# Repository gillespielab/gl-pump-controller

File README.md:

# gl-pump-controller
This board is a SpikeGadgets ECU accessory, which acts as an RJ-45 breakout board for 8 or the DIO ports, and as a pump controller for the other 8 DIO ports in the bank. KiCAD is required to open/edit this project, and can be downloaded at https://www.kicad.org/download/

# Download Instructions
1. Clone the repo `git clone --recursive https://github.com/gillespielab/gl-pump-controller`
2. Open the KiCAD Symbol Editor. Then click: "File" -> "Add Library"
3. Select Global
4. In the prompt, select/open: gl-pump-controller/gl-electronics/symbols/Uploaded.kicad_sym

# BOM
Description | Component Number | Quantity | Part Number/Link
------------- | ------------- | ------------- | -------------
8-bit Buffer | U9-U10 | 2 | [SN74ABT541BPW](https://www.digikey.com/en/products/detail/texas-instruments/SN74ABT541BPW/1575499)
2x10 90deg Header Pins | J11 | 2 | [2057-PH2RA-20-UA-ND](https://www.digikey.com/en/products/detail/adam-tech/PH2RA-20-UA/9830622?s=N4IgTCBcDa4AwFYDsBaACgCTAJQIIrDhQFV8A5AERAF0BfIA)
8x1 RJ-45 Array | J9 | 1 | [432238182](https://www.digikey.com/en/products/detail/molex/0432238182/481095)
SSD Relays | U1-U8 | 8 | [AQY211EHAX](https://www.digikey.com/en/products/detail/panasonic-electric-works/AQY211EHAX/2804732)
1.02kO Resistor | R1-R8 | 8 | [RC1206FR-071K02L](https://www.digikey.com/en/products/detail/yageo/RC1206FR-071K02L/728390)
1uF Ceramic Capacitor | C1-C8 | 8 | [AGC1206X7R101-104KNE-CT](https://www.digikey.com/en/products/detail/venkel/AGC1206X7R101-104KNE-CT/21344624)
10kO Resistor | R9 | 1 | [ERJ-8ENF1002V](https://www.digikey.com/en/products/detail/panasonic-electronic-components/ERJ-8ENF1002V/89059?s=N4IgTCBcDaIAoEYAMA6JBpAYgYQCoFoA5AERAF0BfIA)
100uF Electrolytic Capacitor | C9 | 1 | [50ZLH100MEFC8X11.5](https://www.digikey.com/en/products/detail/rubycon/50ZLH100MEFC8X11-5/3563386)
2P2D Switch | S1 | 1 | [100DP1T2B4M6QE](https://www.digikey.com/en/products/detail/e-switch/100DP1T2B4M6QE/378873)
DC Power Jack | J10 | 1 | [163-179PH-EX](https://www.mouser.com/ProductDetail/Kobiconn/163-179PH-EX?qs=Xb8IjHhkxj5l2UOaIqcGCw%3D%3D)
JST PH-2 Connectors | J1-J8 | 8 | [Amazon](https://www.amazon.com/dp/B0C89MRNSH?ref=fed_asin_title&th=1)

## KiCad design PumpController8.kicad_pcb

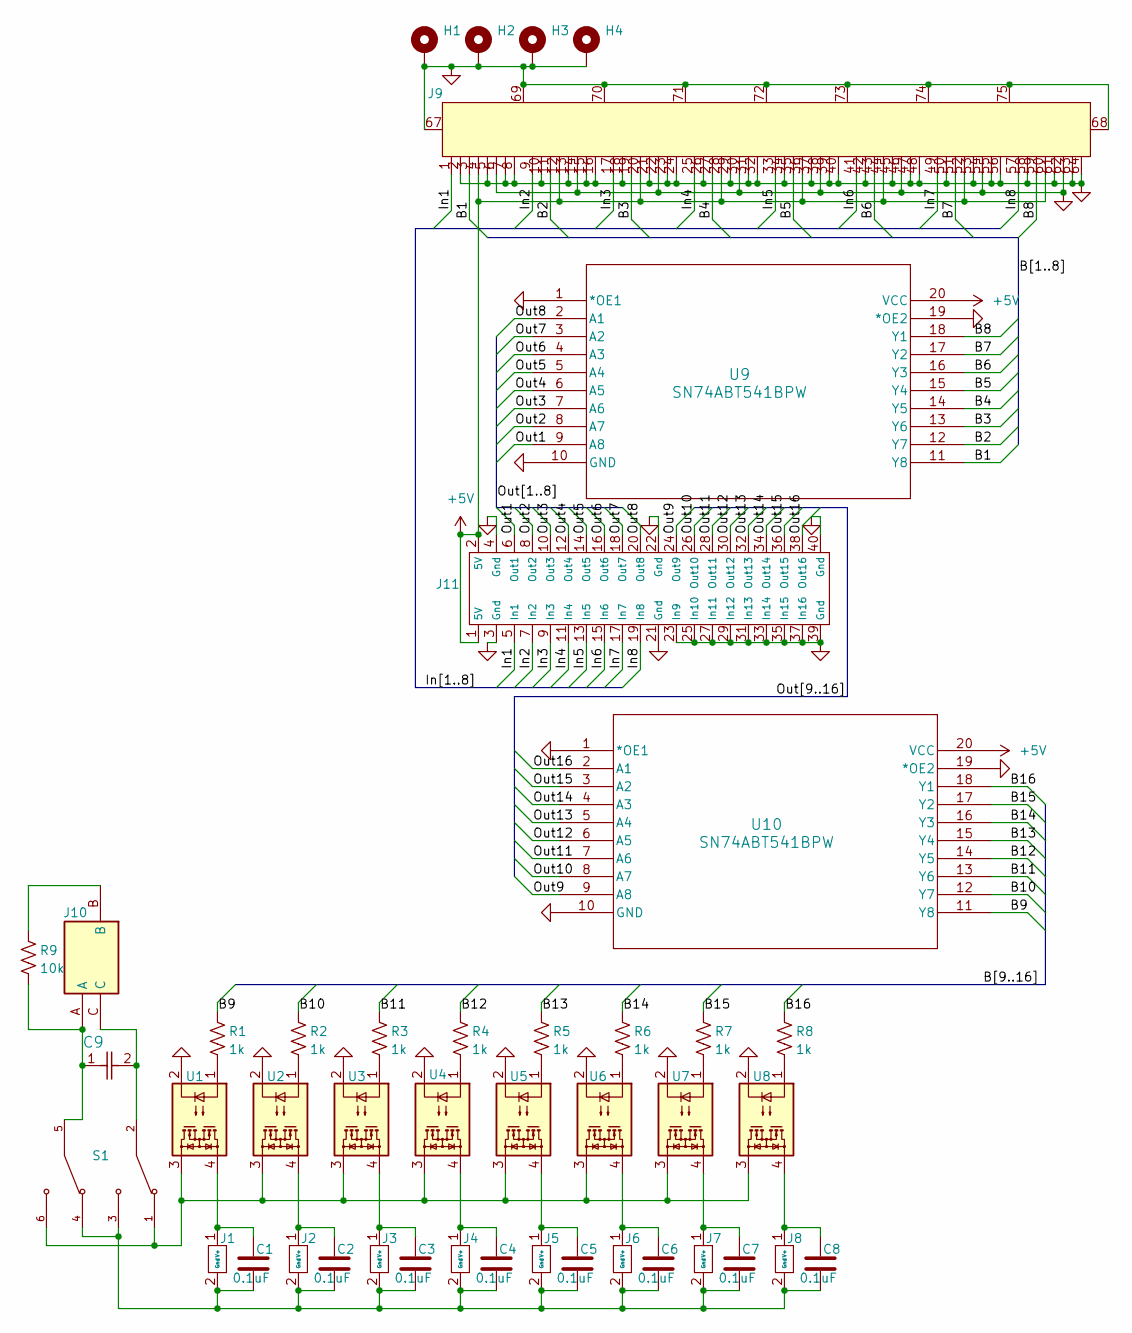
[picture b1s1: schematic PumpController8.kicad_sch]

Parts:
C1, C2, C3, C4, C5, C6, C7, C8: 0.1uF; C_1206_3216Metric_Pad1.33x1.80mm_HandSolder
C9: 50ZLH100MEFC8X11.5; CAP_YX_8X11P5_RUB
H1, H2, H3, H4: MountingHole_Pad; MountingHole_2.7mm_M2.5_ISO7380_Pad
J1, J2, J3, J4, J5, J6, J7, J8: JST-PH 2-Pin Socket; JST-PH 2-Pin Vertical
J9: CONN_43223-8182_MOL
J10: 163-179PH-EX; 163179PHEX; Mouser Part Number 163-179PH-EX
J11: ECU_Header_Pins
R1, R2, R3, R4, R5, R6, R7, R8: 1k; R_1206_3216Metric
R9: 10k; R_1206_3216Metric
S1: 100DP1T2B4M6QE; SW_100DP1T2B4M6QE; PARTREV G
U1, U2, U3, U4, U5, U6, U7, U8: AQY211EHAX
U9, U10: SN74ABT541BPW

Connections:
+5V: J9.4, J9.12, J9.20, J9.28, J9.36, J9.44, J9.52, J9.60, J11.1 (5V), J11.2 (5V), U9.20 (VCC), U10.20 (VCC)
/B1: J9.3, U9.11 (Y8)
/B2: J9.11, U9.12 (Y7)
/B3: J9.19, U9.13 (Y6)
/B4: J9.27, U9.14 (Y5)
/B5: J9.35, U9.15 (Y4)
/B6: J9.43, U9.16 (Y3)
/B7: J9.51, U9.17 (Y2)
/B8: J9.59, U9.18 (Y1)
/B9: R1.1, U10.11 (Y8)
/B10: R2.1, U10.12 (Y7)
/B11: R3.1, U10.13 (Y6)
/B12: R4.1, U10.14 (Y5)
/B13: R5.1, U10.15 (Y4)
/B14: R6.1, U10.16 (Y3)
/B15: R7.1, U10.17 (Y2)
/B16: R8.1, U10.18 (Y1)
/In1: J9.1, J11.5 (In1)
/In2: J9.9, J11.7 (In2)
/In3: J9.17, J11.9 (In3)
/In4: J9.25, J11.11 (In4)
/In5: J9.33, J11.13 (In5)
/In6: J9.41, J11.15 (In6)
/In7: J9.49, J11.17 (In7)
/In8: J9.57, J11.19 (In8)
/Out1: J11.6 (Out1), U9.9 (A8)
/Out2: J11.8 (Out2), U9.8 (A7)
/Out3: J11.10 (Out3), U9.7 (A6)
/Out4: J11.12 (Out4), U9.6 (A5)
/Out5: J11.14 (Out5), U9.5 (A4)
/Out6: J11.16 (Out6), U9.4 (A3)
/Out7: J11.18 (Out7), U9.3 (A2)
/Out8: J11.20 (Out8), U9.2 (A1)
/Out9: J11.24 (Out9), U10.9 (A8)
/Out10: J11.26 (Out10), U10.8 (A7)
/Out11: J11.28 (Out11), U10.7 (A6)
/Out12: J11.30 (Out12), U10.6 (A5)
/Out13: J11.32 (Out13), U10.5 (A4)
/Out14: J11.34 (Out14), U10.4 (A3)
/Out15: J11.36 (Out15), U10.3 (A2)
/Out16: J11.38 (Out16), U10.2 (A1)
GNDS: H1.1, H2.1, H3.1, H4.1, J9.2, J9.5, J9.6, J9.7, J9.8, J9.10, J9.13, J9.14, J9.15, J9.16, J9.18, J9.21, J9.22, J9.23, J9.24, J9.26, J9.29, J9.30, J9.31, J9.32, J9.34, J9.37, J9.38, J9.39, J9.40, J9.42, J9.45, J9.46, J9.47, J9.48, J9.50, J9.53, J9.54, J9.55, J9.56, J9.58, J9.61, J9.62, J9.63, J9.64, J9.67, J9.68, J9.69, J9.70, J9.71, J9.72, J9.73, J9.74, J9.75, J11.3 (Gnd), J11.4 (Gnd), J11.21 (Gnd), J11.22 (Gnd), J11.23 (In9), J11.25 (In10), J11.27 (In11), J11.29 (In12), J11.31 (In13), J11.33 (In14), J11.35 (In15), J11.37 (In16), J11.39 (Gnd), J11.40 (Gnd), U1.2, U2.2, U3.2, U4.2, U5.2, U6.2, U7.2, U8.2, U9.1 (*OE1), U9.10 (GND), U9.19 (*OE2), U10.1 (*OE1), U10.10 (GND), U10.19 (*OE2)
unnamed: C9.1, J10.A, R9.2, S1.5
unnamed: C9.2, J10.C, S1.2
unnamed: C1.2, C2.2, C3.2, C4.2, C5.2, C6.2, C7.2, C8.2, J1.2 (Gnd), J2.2 (Gnd), J3.2 (Gnd), J4.2 (Gnd), J5.2 (Gnd), J6.2 (Gnd), J7.2 (Gnd), J8.2 (Gnd), S1.3, S1.4
unnamed: C1.1, J1.1 (V+), U1.4
unnamed: C2.1, J2.1 (V+), U2.4
unnamed: C3.1, J3.1 (V+), U3.4
unnamed: C4.1, J4.1 (V+), U4.4
unnamed: C5.1, J5.1 (V+), U5.4
unnamed: C6.1, J6.1 (V+), U6.4
unnamed: C7.1, J7.1 (V+), U7.4
unnamed: C8.1, J8.1 (V+), U8.4
unnamed: J10.B, R9.1
unnamed: R1.2, U1.1
unnamed: R2.2, U2.1
unnamed: R3.2, U3.1
unnamed: R4.2, U4.1
unnamed: R5.2, U5.1
unnamed: R6.2, U6.1
unnamed: R7.2, U7.1
unnamed: R8.2, U8.1
unnamed: S1.1, S1.6, U1.3, U2.3, U3.3, U4.3, U5.3, U6.3, U7.3, U8.3

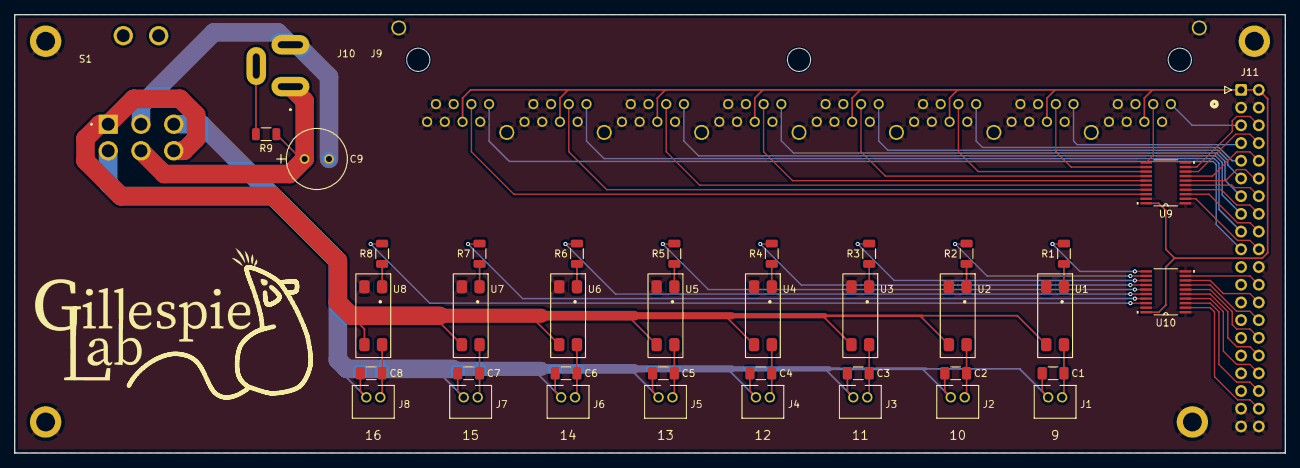
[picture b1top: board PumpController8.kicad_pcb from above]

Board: 2 copper layers, 182.2 x 62.9 mm, 44 parts (0 on the bottom side), 63 nets.

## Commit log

2025-03-04 initial commit (components submodule not included)
2025-03-04 added components module
2025-03-04 components submodule updated
2026-04-18 Update LICENSE
